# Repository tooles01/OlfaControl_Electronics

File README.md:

# OlfaControl_Electronics

## Full System Overview

<br>

<br>

#### Simplified:

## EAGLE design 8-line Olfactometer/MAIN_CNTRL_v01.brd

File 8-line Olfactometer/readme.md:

# 8-line Olfactometer

<br>

<br>

<br>

# Parts to be manufactured
to make a single 8-line unit:
- (x1) top_cover
- (x1) main_manifold_8v
- (x8) main_manifold_cover

<br>

## updates for version 2:
- **main manifold:** mounting holes for main plate on both sides
- **main manifold cover:** 0.01" decrease in length (screw holes are now symmetric)

<br><br>

# Troubleshooting

**Problem:** Inconsistent, "squiggly" odor signal

**Diagnosis:**  Likely something (probably part of the septum) caught in the needle, blocking air flow into the vial

**Solution:** Replace vial input needle

##
**Problem:** Slow odor rise time

**Diagnosis:** Leak

**Solution:** <br>
- Ensure vial cap is on tightly
- Check that isolation valve is completely screwed in
- Replace tubing from vial to mixing chamber

##
**Problem:** Olfactometer not sending back flow values once turned on

**Solution:** <br>
If it is sending back slave addresses:
- Wait 30 seconds or so
- Click "Get Slave Addresses" 1 or 2 times
- If still a problem: Turn 24V power off and back on again, and repeat above steps

If it's not sending back slave addresses:
- Check that PCB is receiving 24V power
- Check that master Arduino I2C pins are correctly connected
- Reupload master Arduino code

##
**Problem:** Zero flow reported, even when proportional valve signal is at max (255)

**Solution:** Replace proportional valve

<!-- Troubleshooting Section as Table-->
<!--
# Troubleshooting

### Hardware/PID testing:

| Problem | Diagnosis | Solution |
| ----------- | ----------- | ----------- |
| Inconsistent, "squiggly" odor signal from PID | Likely something (probably part of the septum) caught in the needle, blocking air flow into the vial | Replace vial input needle |
| Odor signal from one line is significantly higher/lower than others | Variety of possible issues | Check if flow sensor is hitting desired setpoint. <li>If no: Recalibrate flow sensor.</li><li>If yes: Replace proportional valve</li><br>If problem persists, check for leaks.|| Slow odor rise time | Leak | <li>Ensure vial cap is on tightly.</li><li>Replace tubing from vial to mixing chamber.</li><li>Check that isolation valve is completely screwed into mixing chamber.</li>|

<br>

### Electronics/GUI:

| Problem | Solution |
| ----------- | ----------- |
| Olfactometer not sending back flow values once turned on | If it is sending back slave addresses: <li>Wait 30 seconds or so</li><li>Click "Get Slave Addresses" 1 or 2 times</li><li>If still a problem: Turn 24V power off and back on again, and repeat above steps</li><br>If it's not sending back slave addresses: <li>Check that PCB is receiving 24V power</li> <li>Check that master Arduino I2C pins are correctly connected</li><li>Re-upload master Arduino code</li>|
| Zero flow reported from flow sensor, even when proportional valve signal is at max (255) | Replace proportional valve |
-->

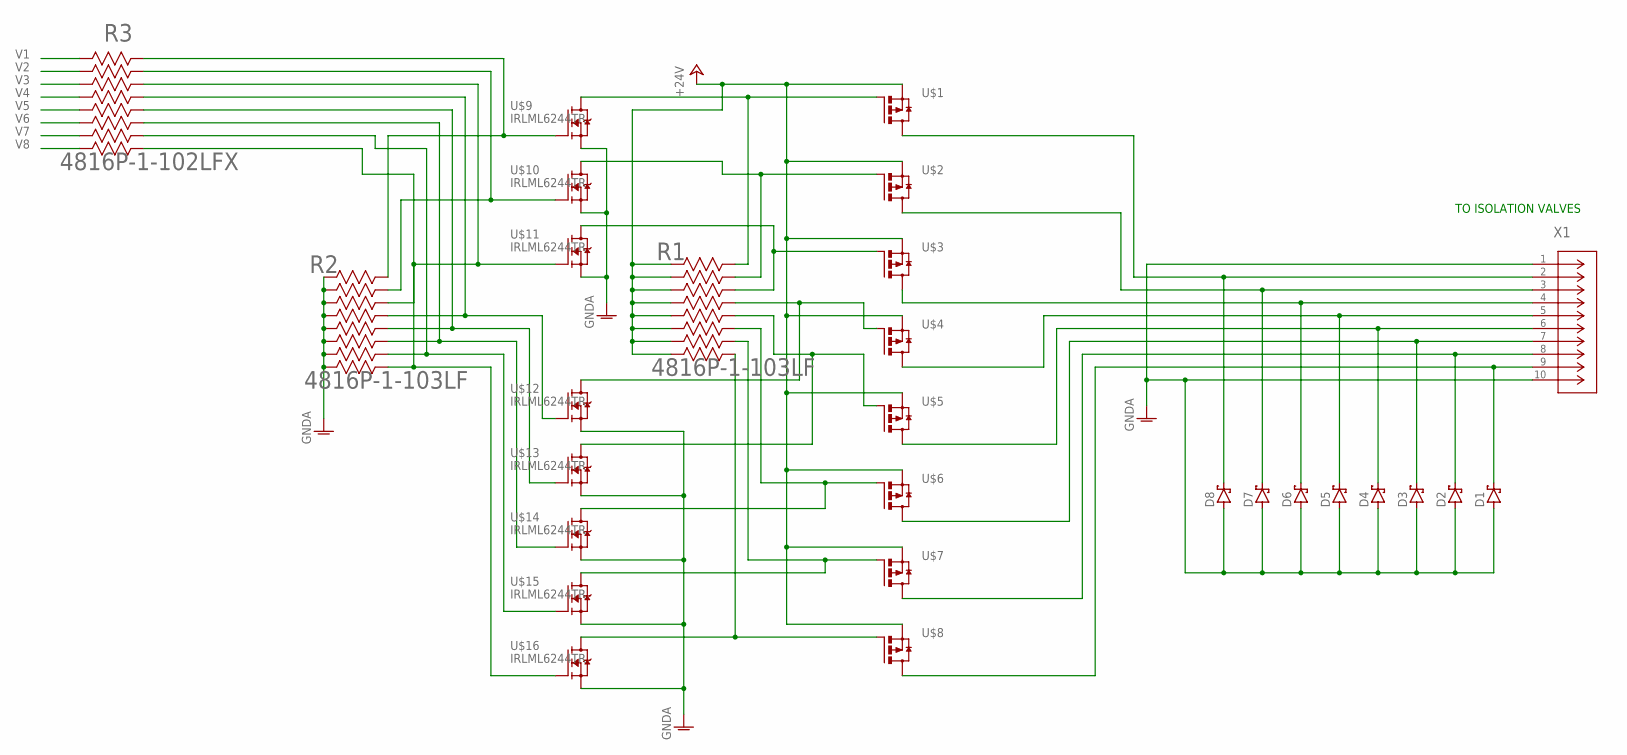
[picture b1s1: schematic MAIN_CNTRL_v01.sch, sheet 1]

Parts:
D1, D2, D3, D4, D5, D6, D7, D8: RB168VYM150FHTR; DIO_RB160VAM_ROM
R1, R2: 4816P-1-103LF; BO_4816P
R3: 4816P-1-102LFX; BO_4816P
U$1, U$2, U$3, U$4, U$5, U$6, U$7, U$8: ZXMP7A17SOT223A; SOT223
U$9, U$10, U$11, U$12, U$13, U$14, U$15, U$16: IRLML6244TR; SOT23
X1: FH52-10S-0.5SH; CONN10_FH52-10S-0.5SH_HIR

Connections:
+24V: R1.1, R1.2, R1.3, R1.4, R1.5, R1.6, R1.7, R1.8, U$1.3 (S), U$2.3 (S), U$3.3 (S), U$4.3 (S), U$5.3 (S), U$6.3 (S), U$7.3 (S), U$8.3 (S); also elsewhere on the board
GNDA: D1.2 (A), D2.2 (A), D3.2 (A), D4.2 (A), D5.2 (A), D6.2 (A), D7.2 (A), D8.2 (A), R2.1, R2.2, R2.3, R2.4, R2.5, R2.6, R2.7, R2.8, U$9.2 (S), U$10.2 (S), U$11.2 (S), U$12.2 (S), U$13.2 (S), U$14.2 (S), U$15.2 (S), U$16.2 (S), X1.1, X1.10; also elsewhere on the board
unnamed: D8.1 (C), U$1.2 (D), U$1.4 (D), X1.2
unnamed: R1.16, U$1.1 (G), U$9.3 (D)
unnamed: R2.16, R3.16, U$9.1 (G)
unnamed: D7.1 (C), U$2.2 (D), U$2.4 (D), X1.3
unnamed: R1.15, U$2.1 (G), U$10.3 (D)
unnamed: R2.15, R3.15, U$10.1 (G)
unnamed: D6.1 (C), U$3.2 (D), U$3.4 (D), X1.4
unnamed: R1.14, U$3.1 (G), U$11.3 (D)
unnamed: D5.1 (C), U$4.2 (D), U$4.4 (D), X1.5
unnamed: R1.13, U$4.1 (G), U$12.3 (D)
unnamed: R2.13, R3.13, U$12.1 (G)
unnamed: D4.1 (C), U$5.2 (D), U$5.4 (D), X1.6
unnamed: R1.12, U$5.1 (G), U$13.3 (D)
unnamed: R2.12, R3.12, U$13.1 (G)
unnamed: D3.1 (C), U$6.2 (D), U$6.4 (D), X1.7
unnamed: R1.11, U$6.1 (G), U$14.3 (D)
unnamed: R2.11, R3.11, U$14.1 (G)
unnamed: D2.1 (C), U$7.2 (D), U$7.4 (D), X1.8
unnamed: R1.10, U$7.1 (G), U$15.3 (D)
unnamed: R2.10, R3.10, U$15.1 (G)
unnamed: D1.1 (C), U$8.2 (D), U$8.4 (D), X1.9
unnamed: R1.9, U$8.1 (G), U$16.3 (D)
unnamed: R2.9, R2.14, R3.9, R3.14, U$11.1 (G), U$16.1 (G)
V1: R3.1; also elsewhere on the board
V2: R3.2; also elsewhere on the board
V3: R3.3; also elsewhere on the board
V4: R3.4; also elsewhere on the board
V5: R3.5; also elsewhere on the board
V6: R3.6; also elsewhere on the board
V7: R3.7; also elsewhere on the board
V8: R3.8; also elsewhere on the board

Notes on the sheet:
TO ISOLATION VALVES

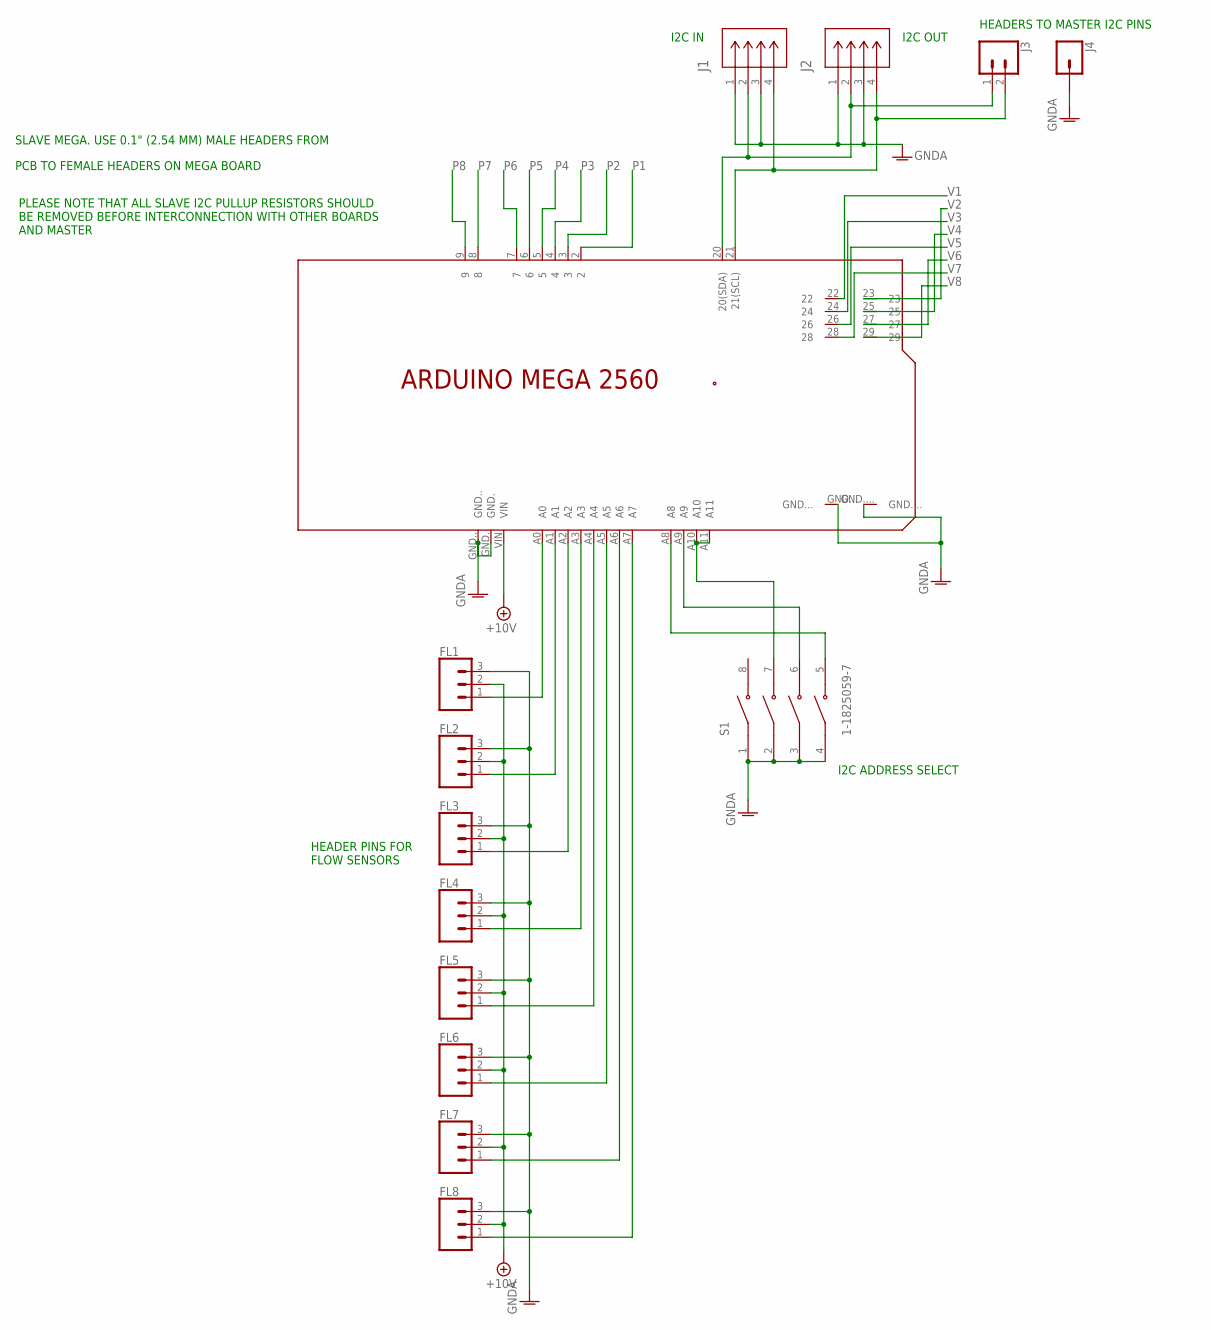
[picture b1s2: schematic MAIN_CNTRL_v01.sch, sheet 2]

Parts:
FL1, FL2, FL3, FL4, FL5, FL6, FL7, FL8: CONN_03_FL; 1X03_FL
J1, J2: MOLEX_436500415; MOLEX_4P_FOOTPRINT
J3: CONN_02; 1X02
J4: CONN_01; 1X01
PCB1: ARDUINO_MEGA2560_HEADERPINSXX; ARDUINO_MEGA2560_ST_FLIPPED_CUTS
S1: 1-1825059-7; SW_1-1825059-7

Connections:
+10V: FL1.2, FL2.2, FL3.2, FL4.2, FL5.2, FL6.2, FL7.2, FL8.2, PCB1.VIN; also elsewhere on the board
GNDA: FL1.3, FL2.3, FL3.3, FL4.3, FL5.3, FL6.3, FL7.3, FL8.3, J1.1, J1.3, J2.1, J2.3, J4.1, PCB1.GND., PCB1.GND.., PCB1.GND..., PCB1.GND...., S1.1, S1.2, S1.3, S1.4; also elsewhere on the board
unnamed: PCB1.A8, S1.5
unnamed: PCB1.A9, S1.6
unnamed: J1.2, J2.2, J3.1, PCB1.20 (20(SDA))
unnamed: PCB1.A10, PCB1.A11, S1.7
unnamed: J1.4, J2.4, J3.2, PCB1.21 (21(SCL))
N$A0: FL1.1, PCB1.A0
N$A1: FL2.1, PCB1.A1
N$A2: FL3.1, PCB1.A2
N$A3: FL4.1, PCB1.A3
N$A4: FL5.1, PCB1.A4
N$A5: FL6.1, PCB1.A5
N$A6: FL7.1, PCB1.A6
N$A7: FL8.1, PCB1.A7
P1: PCB1.2; also elsewhere on the board
P2: PCB1.3; also elsewhere on the board
P3: PCB1.4; also elsewhere on the board
P4: PCB1.5; also elsewhere on the board
P5: PCB1.6; also elsewhere on the board
P6: PCB1.7; also elsewhere on the board
P7: PCB1.8; also elsewhere on the board
P8: PCB1.9; also elsewhere on the board
V1: PCB1.22; also elsewhere on the board
V2: PCB1.23; also elsewhere on the board
V3: PCB1.24; also elsewhere on the board
V4: PCB1.25; also elsewhere on the board
V5: PCB1.26; also elsewhere on the board
V6: PCB1.27; also elsewhere on the board
V7: PCB1.28; also elsewhere on the board
V8: PCB1.29; also elsewhere on the board

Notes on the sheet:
I2C IN
I2C OUT
I2C ADDRESS SELECT
SLAVE MEGA. USE 0.1" (2.54 MM) MALE HEADERS FROM
PCB TO FEMALE HEADERS ON MEGA BOARD
HEADERS TO MASTER I2C PINS
PLEASE NOTE THAT ALL SLAVE I2C PULLUP RESISTORS SHOULD BE REMOVED BEFORE INTERCONNECTION WITH OTHER BOARDS AND MASTER
HEADER PINS FOR FLOW SENSORS

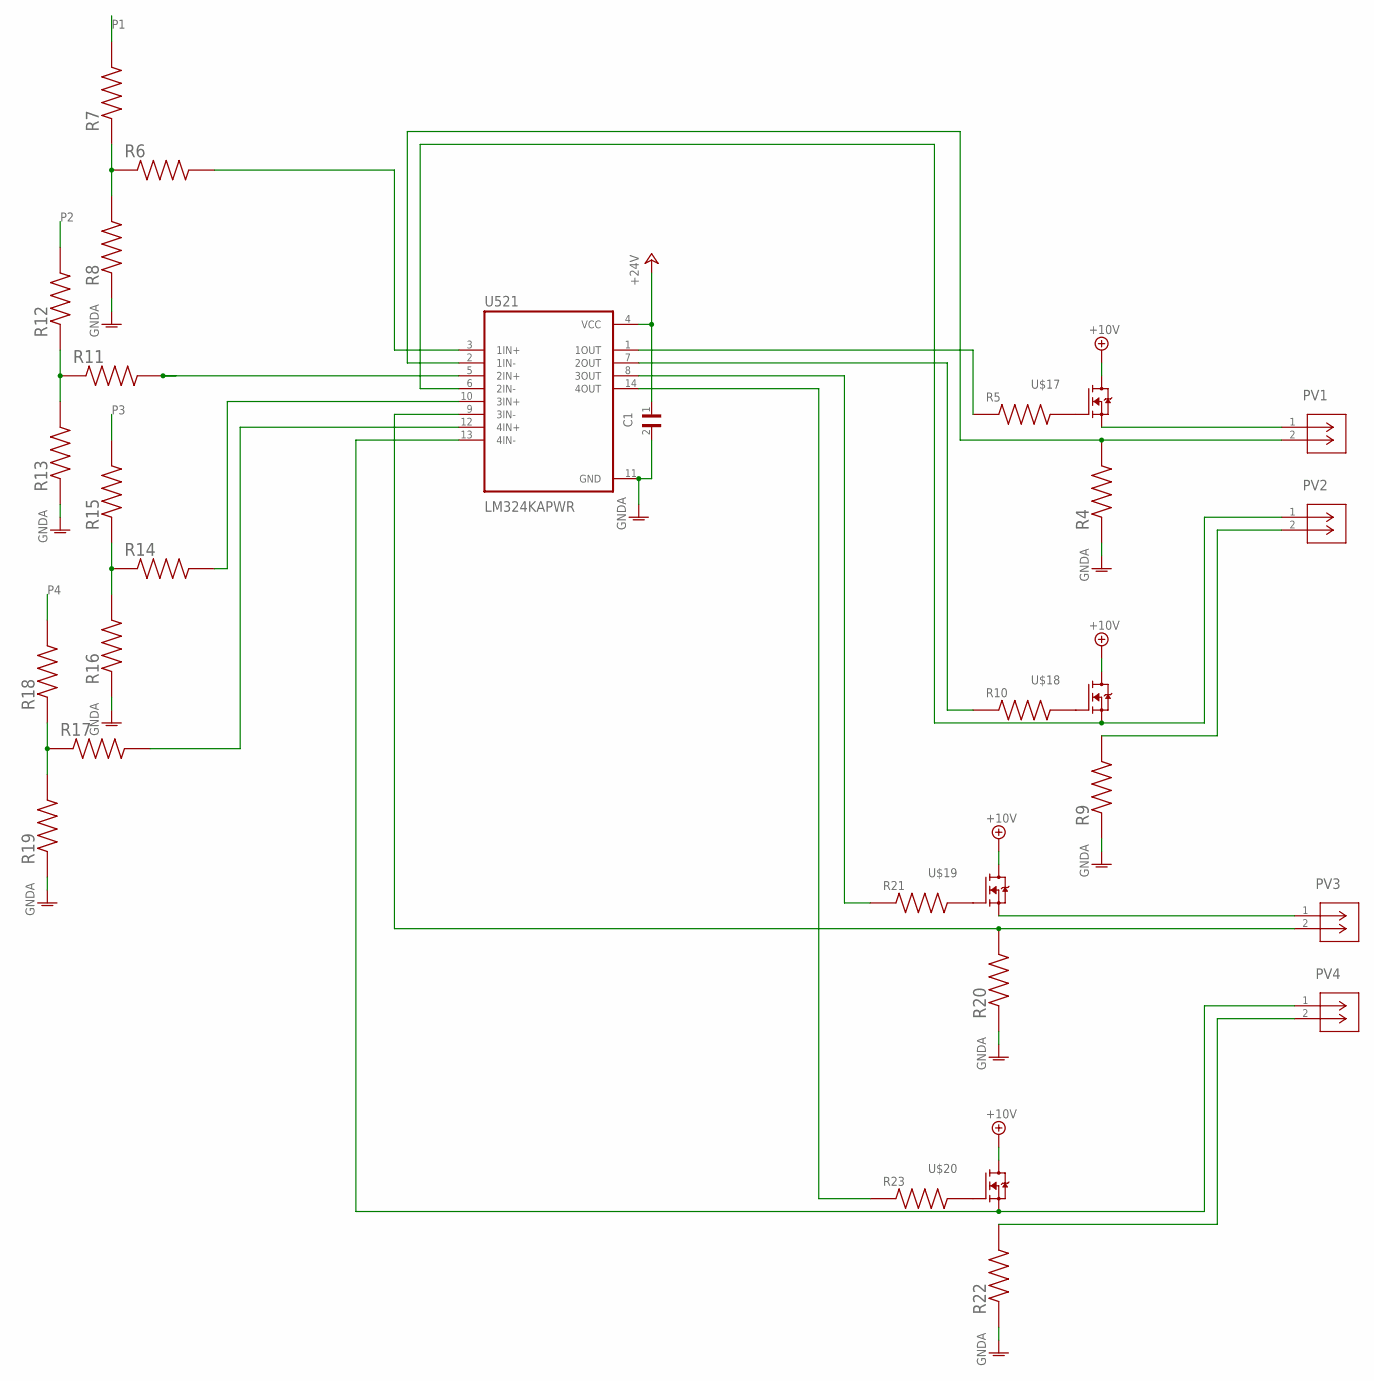
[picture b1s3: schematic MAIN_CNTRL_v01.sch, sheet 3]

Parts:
C1: CGA3E2X7R1H104M080AD; CAP_1608_TDK
PV1, PV2, PV3, PV4: MOLEX_2P_PVALVES
R4, R9, R20, R22: CRCW12062R20FKEA; RESC3116X60N
R5, R10, R21, R23: ERJPA3F1001V; RES_ERJPA3F1001V
R6, R11, R14, R17: SR0603FR-7T100KL; RESC1608X55N
R7, R12, R15, R18: SR0603FR-7T2K2L; RESC1608X55N
R8, R13, R16, R19: RCS0603120RFKEA; RESC1508X50N
U521: LM324KAPWR; SOP65P640X120-14N
U$17, U$18, U$19, U$20: IRLML6244TR; SOT23

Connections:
+10V: U$17.3 (D), U$18.3 (D), U$19.3 (D), U$20.3 (D); also elsewhere on the board
+24V: C1.1, U521.4 (VCC); also elsewhere on the board
GNDA: C1.2, R4.1, R8.1, R9.1, R13.1, R16.1, R19.1, R20.1, R22.1, U521.11 (GND); also elsewhere on the board
unnamed: R5.2, U$17.1 (G)
unnamed: R5.1, U521.1 (1OUT)
unnamed: R6.2, U521.3 (1IN+)
unnamed: R6.1, R7.1, R8.2
unnamed: R10.1, U521.7 (2OUT)
unnamed: R10.2, U$18.1 (G)
unnamed: R11.1, R12.1, R13.2
unnamed: R11.2, U521.5 (2IN+)
unnamed: R14.1, R15.1, R16.2
unnamed: R14.2, U521.10 (3IN+)
unnamed: R17.1, R18.1, R19.2
unnamed: R17.2, U521.12 (4IN+)
unnamed: R21.2, U$19.1 (G)
unnamed: R21.1, U521.8 (3OUT)
unnamed: R23.2, U$20.1 (G)
unnamed: R23.1, U521.14 (4OUT)
N$PV1_1: PV1.1, U$17.2 (S)
N$PV1_2: PV1.2, R4.2, U521.2 (1IN-)
N$PV2_1: PV2.1, U521.6 (2IN-), U$18.2 (S)
N$PV2_2: PV2.2, R9.2
N$PV3_1: PV3.1, U$19.2 (S)
N$PV3_2: PV3.2, R20.2, U521.9 (3IN-)
N$PV4_1: PV4.1, U521.13 (4IN-), U$20.2 (S)
N$PV4_2: PV4.2, R22.2
P1: R7.2; also elsewhere on the board
P2: R12.2; also elsewhere on the board
P3: R15.2; also elsewhere on the board
P4: R18.2; also elsewhere on the board

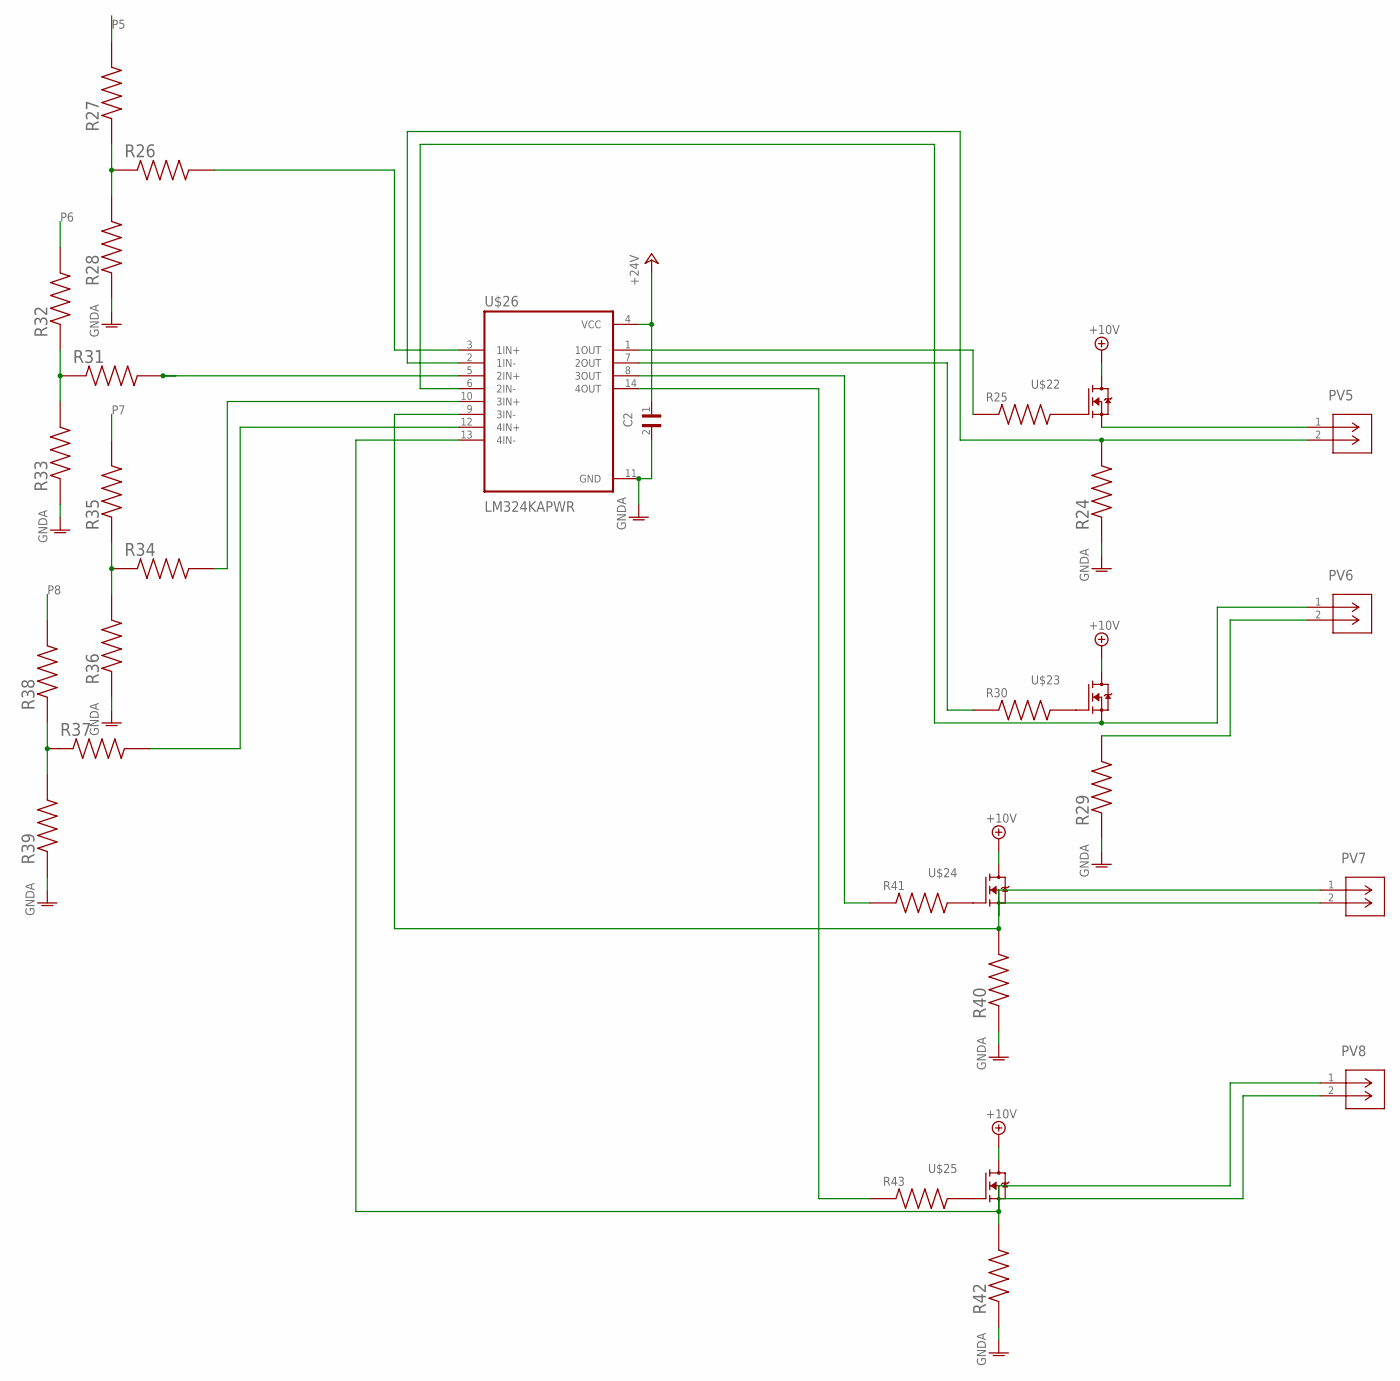
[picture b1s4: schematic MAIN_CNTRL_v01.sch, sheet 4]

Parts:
C2: CGA3E2X7R1H104M080AD; CAP_1608_TDK
PV5, PV6, PV7, PV8: MOLEX_2P_PVALVES
R24, R29, R40, R42: CRCW12062R20FKEA; RESC3116X60N
R25, R30, R41, R43: ERJPA3F1001V; RES_ERJPA3F1001V
R26, R31, R34, R37: SR0603FR-7T100KL; RESC1608X55N
R27, R32, R35, R38: SR0603FR-7T2K2L; RESC1608X55N
R28, R33, R36, R39: RCS0603120RFKEA; RESC1508X50N
U$22, U$23, U$24, U$25: IRLML6244TR; SOT23
U$26: LM324KAPWR; SOP65P640X120-14N

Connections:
+10V: U$22.3 (D), U$23.3 (D), U$24.3 (D), U$25.3 (D); also elsewhere on the board
+24V: C2.1, U$26.4 (VCC); also elsewhere on the board
GNDA: C2.2, R24.1, R28.1, R29.1, R33.1, R36.1, R39.1, R40.1, R42.1, U$26.11 (GND); also elsewhere on the board
unnamed: R25.2, U$22.1 (G)
unnamed: R25.1, U$26.1 (1OUT)
unnamed: R26.1, R27.1, R28.2
unnamed: R30.2, U$23.1 (G)
unnamed: R26.2, U$26.3 (1IN+)
unnamed: R31.1, R32.1, R33.2
unnamed: R31.2, U$26.5 (2IN+)
unnamed: R34.1, R35.1, R36.2
unnamed: R34.2, U$26.10 (3IN+)
unnamed: R37.1, R38.1, R39.2
unnamed: R37.2, U$26.12 (4IN+)
unnamed: R41.2, U$24.1 (G)
unnamed: R41.1, U$26.8 (3OUT)
unnamed: R43.2, U$25.1 (G)
unnamed: R43.1, U$26.14 (4OUT)
unnamed: R30.1, U$26.7 (2OUT)
N$PV5_1: PV5.1, U$22.2 (S)
N$PV5_2: PV5.2, R24.2, U$26.2 (1IN-)
N$PV6_1: PV6.1, U$23.2 (S), U$26.6 (2IN-)
N$PV6_2: PV6.2, R29.2
N$PV7_1: PV7.1, U$24.2 (S)
N$PV7_2: PV7.2, R40.2, U$26.9 (3IN-)
N$PV8_1: PV8.1, U$25.2 (S), U$26.13 (4IN-)
N$PV8_2: PV8.2, R42.2
P5: R27.2; also elsewhere on the board
P6: R32.2; also elsewhere on the board
P7: R35.2; also elsewhere on the board
P8: R38.2; also elsewhere on the board

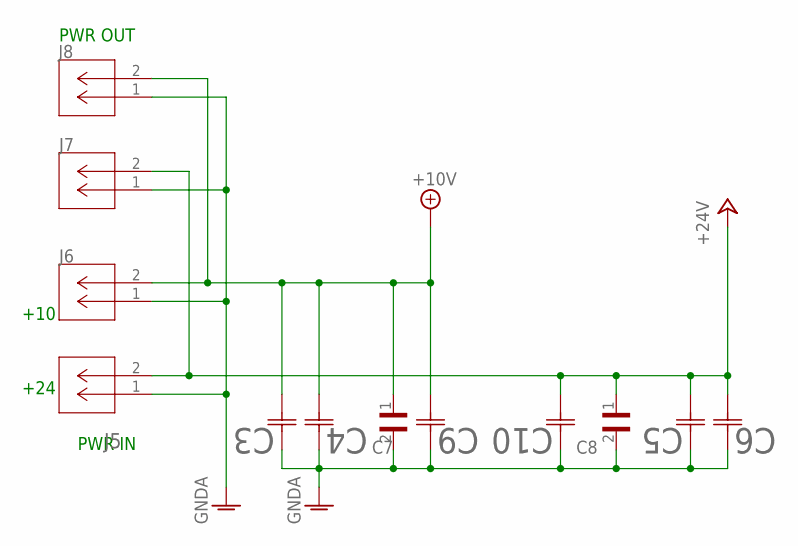
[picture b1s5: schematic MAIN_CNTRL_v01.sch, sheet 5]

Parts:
C3, C4, C5, C6: 50THV100M10X10.5; CAP_J-V_10X10P5_RUB
C7, C8: CGA3E2X7R1H104M080AD; CAP_1608_TDK
C9, C10: CGA3E2X7R1H103K080AE; CAP_1608_TDK
J5, J6, J7, J8: MOLEX_436500215; MOLEX_2P_FOOTPRINT

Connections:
+10V: C3.2, C4.2, C7.1, C9.2, J6.2, J8.2; also elsewhere on the board
+24V: C5.2, C6.2, C8.1, C10.2, J5.2, J7.2; also elsewhere on the board
GNDA: C3.1, C4.1, C5.1, C6.1, C7.2, C8.2, C9.1, C10.1, J5.1, J6.1, J7.1, J8.1; also elsewhere on the board

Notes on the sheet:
PWR IN
PWR OUT
+24
+10

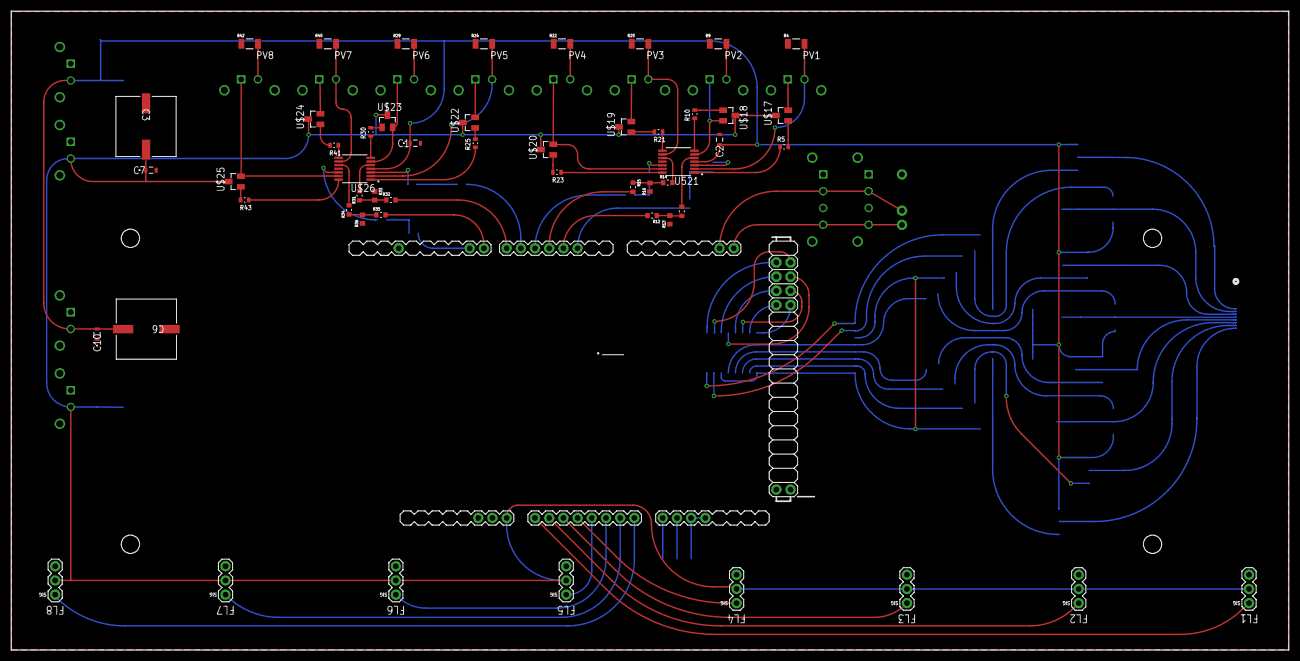
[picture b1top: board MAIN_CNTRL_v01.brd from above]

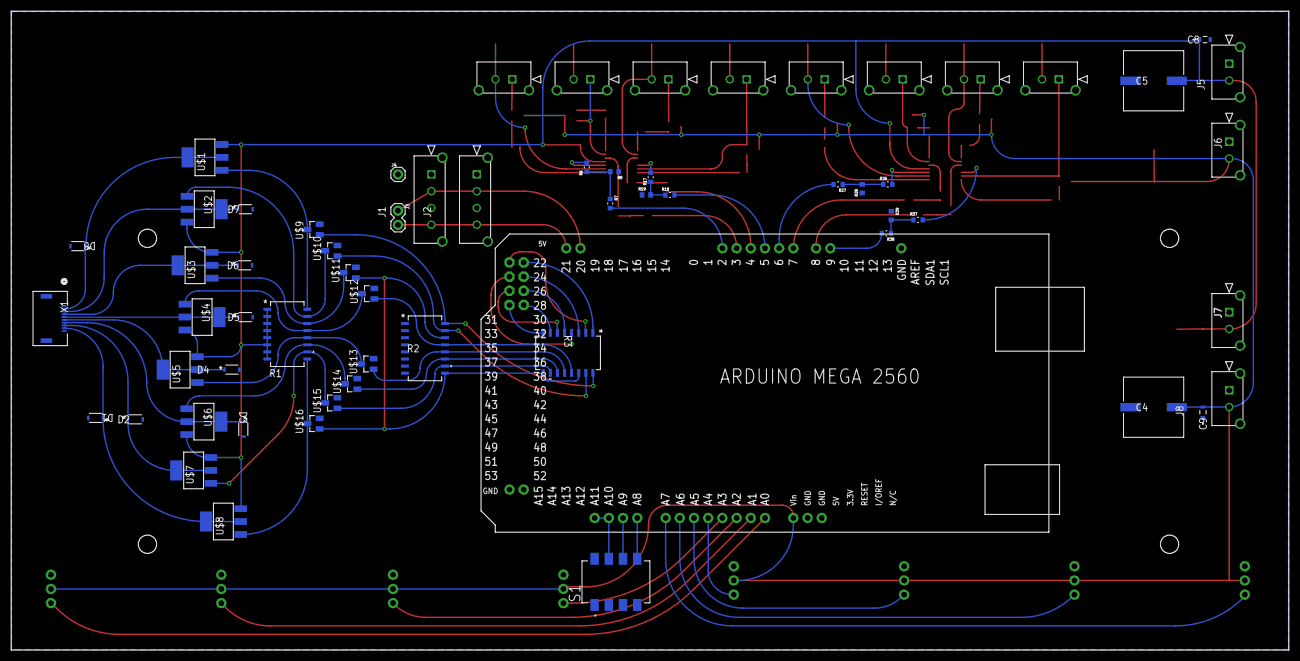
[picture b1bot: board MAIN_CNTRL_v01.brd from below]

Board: 2 copper layers, 228.6 x 114.3 mm, 114 parts (62 on the bottom side), 103 nets.

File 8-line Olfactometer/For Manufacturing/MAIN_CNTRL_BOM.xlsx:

Item # | Designator | Qty | Manufacturer | Mfg. Part # | Distributor | Distrib. Part # | Description | Package/Footprint | Type | Notes
1 | J4 | 1 | 3M | 951101-8622-AR | Digi-Key | 3M156413-01-ND | CONN HEADER VERT 1POS |  | Through Hole
2 | J3 | 1 | 3M | 961102-6404-AR | Digi-Key | 3M9457-02-ND | CONN HEADER VERT 2POS 2.54MM |  | Through Hole
3 | FL1, FL2, FL3, FL4, FL5, FL6, FL7, FL8 | 8 | Sullins Connector Solutions | PPPC031LFBN-RC | Digi-Key | S7036-ND | CONN HDR 3POS 0.1 GOLD PCB |  | Through Hole
4 | S1 | 1 | TE Connectivity | 1-1825059-7 | Digi-Key | 1-1825059-7-ND | SWITCH SLIDE DIP SPST 25MA 24V | * see attached datasheet | Surface Mount
5 | R3 | 1 | Bourns Electronics | 4816P-1-102LF | Digi-Key | 4816P-1-102LFCT-ND | RES ARRAY 8 RES 1K OHM 16SOIC | 16-SOIC (0.220", 5.59mm Width) | Surface Mount
6 | R1, R2 | 2 | Bourns Electronics | 4816P-1-103LF | Digi-Key | 4816P-1-103LFCT-ND | RES ARRAY 8 RES 10K OHM 16SOIC | 16-SOIC (0.220", 5.59mm Width) | Surface Mount
7 | C3, C4, C5, C6 | 4 | Rubycon | 50THV100M10X10.5 | Digi-Key | 1189-2059-1-ND | CAP ALUM 100UF 20% 50V SMD | Radial, Can - SMD | Surface Mount
8 | PCB1 | 1 |  |  |  |  |  |  | Through Hole
9 | C9, C10 | 2 | TDK | CGA3E2X7R1H103K080AE | Digi-Key | 445-15955-1-ND | CAP CER 10000PF 50V X7R 0603 | 0603 (1608 Metric) | Surface Mount
10 | C1, C2, C7, C8 | 4 | TDK Corporation | CGA3E2X7R1H104M080AD | Digi-Key | 445-9834-1-ND | CAP CER 0.1UF 50V X7R 0603 EPOXY | 0603 (1608 Metric) | Surface Mount
11 | R4, R9, R20, R22, R24, R29, R40, R42 | 8 | Vishay Dale | CRCW12062R20FKEA | Digi-Key | 541-2.20FFCT-ND | RES SMD 2.2 OHM 1% 1/4W 1206 | 1206 (3216 Metric) | Surface Mount
12 | R5, R10, R21, R23, R25, R30, R41, R43 | 8 | Panasonic | ERJPA3F1001V | Digi-Key | P1.0KBYCT-ND | RES SMD 1K OHM 1% 1/4W 0603 | 0603 (1608 Metric) | Surface Mount
13 | X1 | 1 | Hirose Electric Co Ltd | FH52-10S-0.5SH | Digi-Key | H126109CT-ND | CONN FFC BOTTOM 10POS 0.50MM R/A | * see attached datasheet | Surface Mount
14 | U$9, U$10, U$11, U$12, U$13, U$14, U$15, U$16, U$17, U$18, U$19, U$20, U$22, U$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 | 16 | Infineon Technologies | IRLML6244TRPBF | Digi-Key | IRLML6244TRPBFCT-ND | MOSFET N-CH 20V 6.3A SOT23 | Micro3 (SOT-23) | Surface Mount
15 | U$26, U521 | 2 | Texas Instruments | LM324KAPWR | Digi-Key | 296-18449-1-ND | IC OPAMP GP 4 CIRCUIT 14TSSOP | 14-TSSOP (0.173", 4.40mm Width) | Surface Mount
16 | PV1, PV2, PV3, PV4, PV5, PV6, PV7, PV8 | 8 | Molex | 436500215 | Digi-Key | WM1917-ND | CONN HEADER VERT 2POS 3MM |  | Through Hole
17 | J5, J6, J7, J8 | 4 | Molex | 436500215 | Digi-Key | WM1917-ND | CONN HEADER VERT 2POS 3MM |  | Through Hole
18 | J1, J2 | 2 | Molex | 436500415 | Digi-Key | WM1919-ND | CONN HEADER VERT 4POS 3MM |  | Through Hole
19 | D1, D2, D3, D4, D5, D6, D7, D8 | 8 | ROHM Semiconductor | RB168VYM150FHTR | Digi-Key | RB168VYM150FHCT-ND | SCHOTTKY BARRIER DIODE (AEC-Q101 | 2-SMD, Flat Lead | Surface Mount
20 | R8, R13, R16, R19, R28, R33, R36, R39 | 8 | Vishay | RCS0603120RFKEA | Digi-Key | 541-10426-1-ND | RES SMD 120 OHM 1% 1/4W 0603 | 0603 (1608 Metric) | Surface Mount
21 | R6, R11, R14, R17, R26, R31, R34, R37 | 8 | Yageo | SR0603FR-7T100KL | Digi-Key | YAG5821CT-ND | RES 100K OHM 1% 1/4W 0603 | 0603 (1608 Metric) | Surface Mount
22 | R7, R12, R15, R18, R27, R32, R35, R38 | 8 | Yageo | SR0603FR-7T2K2L | Digi-Key | YAG5834CT-ND | RES 2.2K OHM 1% 1/4W 0603 | 0603 (1608 Metric) | Surface Mount
23 | U$1, U$2, U$3, U$4, U$5, U$6, U$7, U$8 | 8 | Diodes Incorporated | ZXMP7A17GQTA | Digi-Key | ZXMP7A17GQTADICT-ND | MOSFET P-CH 70V 2.6A SOT223 | SOT223 | Surface Mount

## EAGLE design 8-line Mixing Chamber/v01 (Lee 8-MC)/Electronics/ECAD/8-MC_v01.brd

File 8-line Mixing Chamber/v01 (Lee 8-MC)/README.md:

# Lee Mixing Chamber

<br><br>

# Parts to be manufactured

to make a single unit:

- (x1) Lee 8-MC cover
- (x1) Lee 8-MC heart

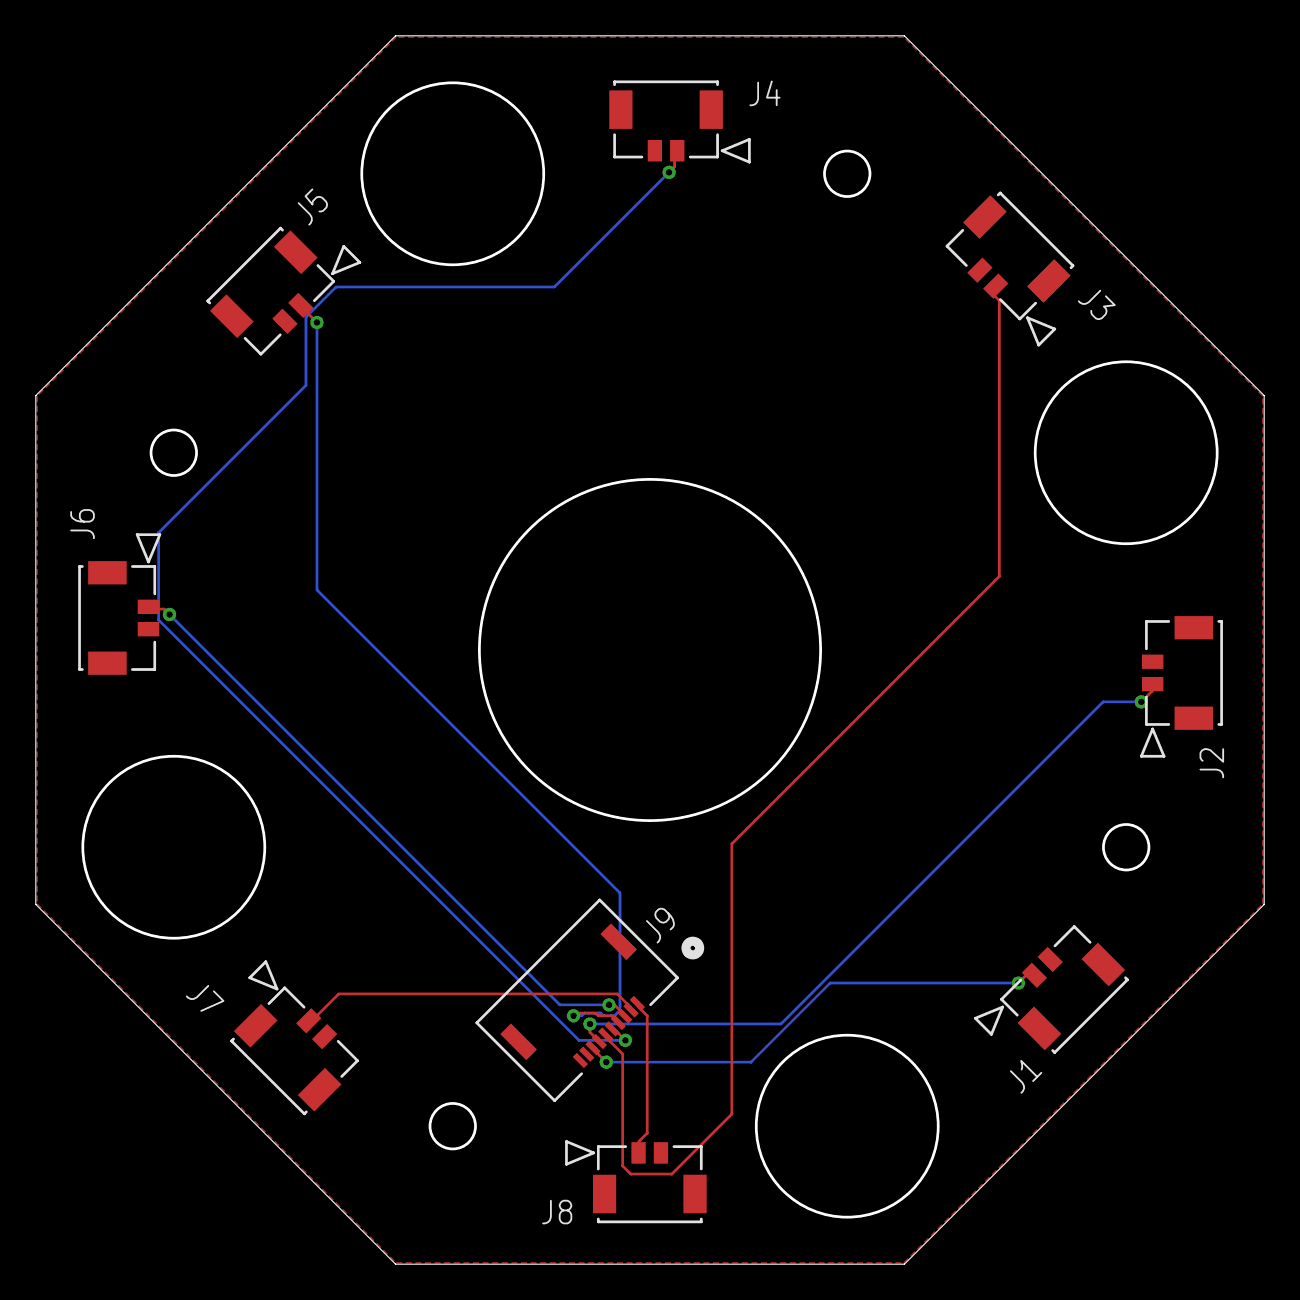
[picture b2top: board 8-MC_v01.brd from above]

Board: 2 copper layers, 68.4 x 68.4 mm, 9 parts (0 on the bottom side), 9 nets.

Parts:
J1, J2, J3, J4, J5, J6, J7, J8: 5055670281CON_5055670281; CON_5055670281
J9: FH52-10S-0.5SHCONN10_FH52-10S-0.5SH_HIR; CONN10_FH52-10S-0.5SH_HIR

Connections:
GND: J1.2, J1.3, J1.4, J2.2, J2.3, J2.4, J3.2, J3.3, J3.4, J4.2, J4.3, J4.4, J5.2, J5.3, J5.4, J6.2, J6.3, J6.4, J7.2, J7.3, J7.4, J8.2, J8.3, J8.4
unnamed: J8.1, J9.1
unnamed: J7.1, J9.2
unnamed: J6.1, J9.3
unnamed: J5.1, J9.4
unnamed: J1.1, J9.8
unnamed: J2.1, J9.7
unnamed: J3.1, J9.6
unnamed: J4.1, J9.5

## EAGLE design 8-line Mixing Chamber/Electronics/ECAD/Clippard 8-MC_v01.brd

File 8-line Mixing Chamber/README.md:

# Clippard Mixing Chamber

<br>

<br>

<br><br>

# Parts to be manufactured

to make a single unit:

- (x1) Clippard 8-MC cover
- (x1) Clippard 8-MC heart

<br><br>

## updates for version 2:
- **Clippard 8-MC cover**
    - Slightly different location of PCB mounting holes
- **Clippard 8-MC heart**
    - Removed bottom depression, outlet changed from a male thread to an NResearch (1/4-28) female hole (matches the vial inlet holes)
    - Odor (vial) inlet ID changed
    - Odor input hole (from the bottom) was previously not aligned with its connecting inlet hole (horizontal) - tied geometries together

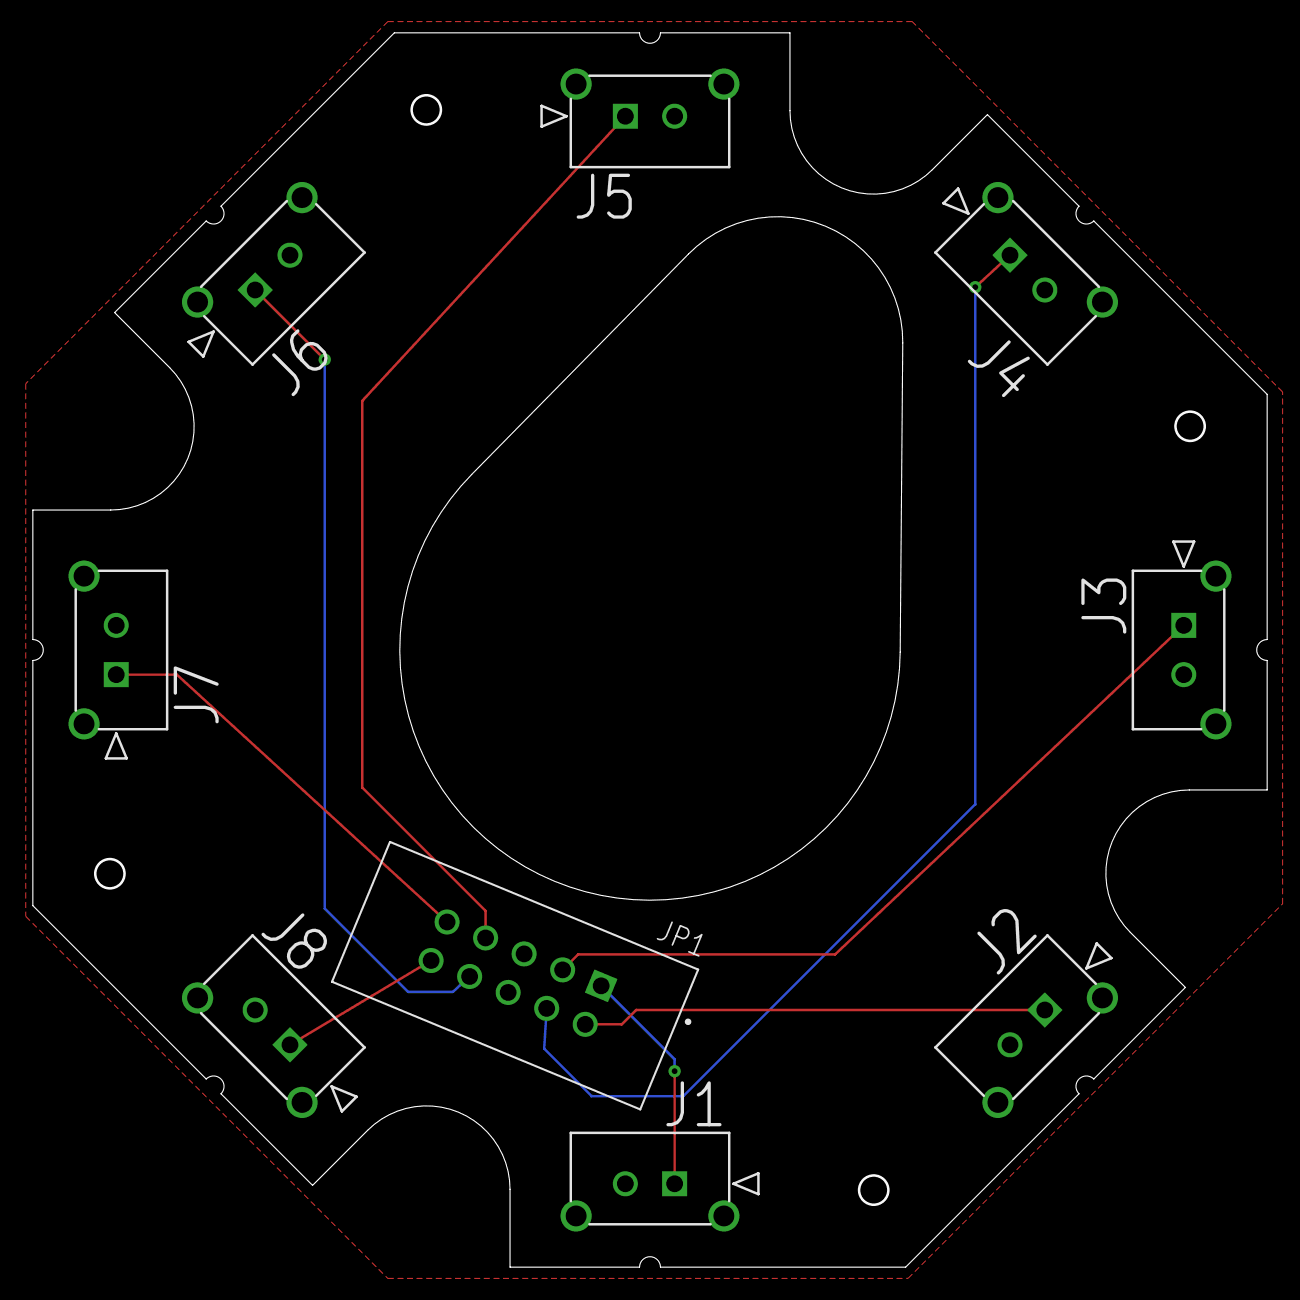
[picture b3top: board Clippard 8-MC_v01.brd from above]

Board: 2 copper layers, 75.0 x 75.0 mm, 9 parts (0 on the bottom side), 9 nets.

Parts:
J1, J2, J3, J4, J5, J6, J7, J8: MOLEX_436500215C; MOLEX_2P_FOOTPRINT_CENTERED
JP1: CONN_10P_TE_1761681-3C; CONN_10P_TE_1761681-3_SE_FOR_V02_CENTERED

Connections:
GND1: J1.2, J2.2, J3.2, J4.2, J5.2, J6.2, J7.2, J8.2, JP1.GND, JP1.GND.
V1: J1.1, JP1.V1
V2: J2.1, JP1.V2
V3: J3.1, JP1.V3
V4: J4.1, JP1.V4
V5: J5.1, JP1.V5
V6: J6.1, JP1.V6
V7: J7.1, JP1.V7
V8: J8.1, JP1.V8

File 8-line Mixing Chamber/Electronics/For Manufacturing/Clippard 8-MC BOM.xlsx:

Item # | Designator | Qty | Manufacturer | Mfg Part # | Description / Value | Package / Footprint | Type | Instructions / Notes
1 | JP1 | 1 | TE Connectivity AMP Connectors | 1761681-3 | Connector Header Through Hole 10 position 0.100 (2.54mm)" |  | Through Hole
2 | J1, J2, J3, J4, J5, J6, J7, J8 | 8 | Molex | 0436500215 | Connector Header Through Hole 2 position 0.118 (3.00mm)" |  | Through Hole

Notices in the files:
parts and their libraries:
COPYRIGHT: Copyright (C) 2021 Ultra Librarian. All rights reserved.
COPYRIGHT: Copyright (C) 2018 Accelerated Designs. All rights reserved
COPYRIGHT: Copyright (C) 2022 Ultra Librarian. All rights reserved.
